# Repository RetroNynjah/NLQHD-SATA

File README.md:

# RetroNinja NLQHD-SATA
<br/>

A SATA-disk interface for the Commodore IEC-bus based on the NLQHD-lite design by Jochen Adler a.k.a. NLQ. The original design, documentation, firmware and source code can be found at [nlq.de](http://nlq.de).

## NLQ-HD
The NLQHD disk interface is a JiffyDOS compatible hard disk controller for the IEC bus. It was designed by Jochen Adler who also wrote the firmware. It supports a partition size of up to 128GB. Larger hard drives can be used but the partition size can not be greater than 128GB. 
The file system used is FAT32 so with a SATA-USB adapter it's easy to unplug and connect the SATA drive to a computer for quick file transfers.  
It should work with all Commodore 8-bit computers using an IEC bus. The drive can in theory be used with a stock kernal in the computer but the standard commands for navigating directories uses the command channel and are pretty cumbersome to use. A JiffyDOS kernal or one of it's derivatives such as S-JiffyDOS or JaffyDOS is pretty much required.

## NLQHD-SATA
This SATA version is a somewhat simplified design in that it doesn't have the same level of over-voltage protection as the original design has. The reason is that I wanted to keep the size of the design down (70x58mm) to fit in a 3D-printed enclosure. It also can't be powered by 1541-II PSU so the protection is less necessary than on the original design. I recommend that this version is powered using a decent quality 12V DC adapter with a center positive barrel connector.  
I have also removed the debugging/programming dip switches so the programming software for the C64 can't be used for flashing the firmware. I don't think it's safe to use so don't even try to use it!  
Instead I have added an ICSP programming header so that the firmware can be programmed in circuit using any AVR programmer such as AVR-ISP, USBASP or even an Arduino (Arduino as ISP). More importantly I've also added a JMH330 PATA-SATA bridge so that the interface can be used with more available and reliable SSD drives without an extra adapter. All SATA drives should be possible to use, from older 3.5" rotational drives to the newer 2.5" SSD drives. 
I replaced the sometimes hard-to-find 5 Volt regulator with integrated components based around an LM2596 voltage regulator. These have unfortunately also became harder to find from reliable sources at the time of writing but are easy to find on eBay or AliExpress. 3.3V and 1.8V voltage regulators have been added to drive the SATA bridge.  
I have made a separate front panel for the control buttons and LEDs. It connects to the mainboard using a 5 pin connector and can easily be replaced by a different panel if you need a different shape.  

<br/>
<br/>

I have also created a simple front panel board with buttons and status LEDs.  
This separate board should be pretty easy to modify to suite your own needs.
<br/>

## Mainboard BOM

|Parts|Device|Value|Qty|
|-----|-----|-----|-----|
|C101, C102, C103, C104, C201, C202, C203, C204, C205, C206, C301|Ceramic capacitor 0805|100n|11|
|C11, C12|Ceramic capacitor 0805|100p|2|
|C207, C208, C209, C210|Ceramic capacitor 0805|10n|4|
|C211|Ceramic capacitor 0805|1u 10V|1|
|C401|Electrolytic capacitor SMD 6.3X7.7|100u 25V|1|
|C403|Electrolytic capacitor SMD 6.3X7.7|220u 10V|1|
|C404|Ceramic capacitor 0805|10n(*)|1|
|C501, C502, C601, C602|Polarized tantalum capacitor 1206|10uF 10V|4|
|C9, C10, C212, C213|Ceramic capacitor 0805|22p|4|
|D1, D401|Schottky diode 3A SOD-123FL|S34|2|
|D12|General purpose diode SOD-323F|1N4148WSF|1|
|J1, J2|DIN-6 Female PCB-mount||2|
|J3|Molex 22-pin SATA host connector|0470184000|1|
|J4|DC Barrel Jack|PJ-002A|1|
|J5|Shrouded male JST header|5-pin, 2.0mm|1|
|J6|Pin header|2x3-pin, 2.54mm|1|
|JP1|Jumper or power switch|2-pin, 2.54mm|1|
|L1|Inductor 10x11mm|33uH|1|
|R11|Resistor 0805|10k|1|
|R201|Resistor 0805|12k|1|
|R202|Resistor 0805|47k|1|
|R203|Resistor 0805|1M|1|
|R401|Resistor 0805|1k (*)|1|
|R402|Resistor 0805|3k1/0R(*)|1|
|R5, R6|Resistor 0805|100R|2|
|SW1|Tact. switch right angle|6.0x5.0x8.5mm|1|
|U1|Microcontroller TQFP-44|ATmega1284(P)|1|
|U2|PATA-SATA bridge TQFP-64|JMH330|1|
|U3|Hex buffers/drivers SOIC14|74LS07|1|
|U4|Switching regulator TO263-5|LM2596 (AP1501A)|1|
|U5|Volt regulator 3.3V SOT-223|LD1117-3.3|1|
|U6|Volt regulator 1.8V SOT-223|LD1117-1.8|1|
|Y1|Crystal ECX-32|8MHz|1|
|Y2|Crystal ECX-32|25MHz|1|

(*) Only for Adjustable LM2596.
If using a fixed 5V LM2596: Do NOT install R401 and C404 and use a 0 Ohm resistor at R402

There are several variants of 6-pin DIN connectors with different foot prints. I have tried to accommodate them all in one single foot print. Let me know if you have a DIN connector that still doesn't fit this board.

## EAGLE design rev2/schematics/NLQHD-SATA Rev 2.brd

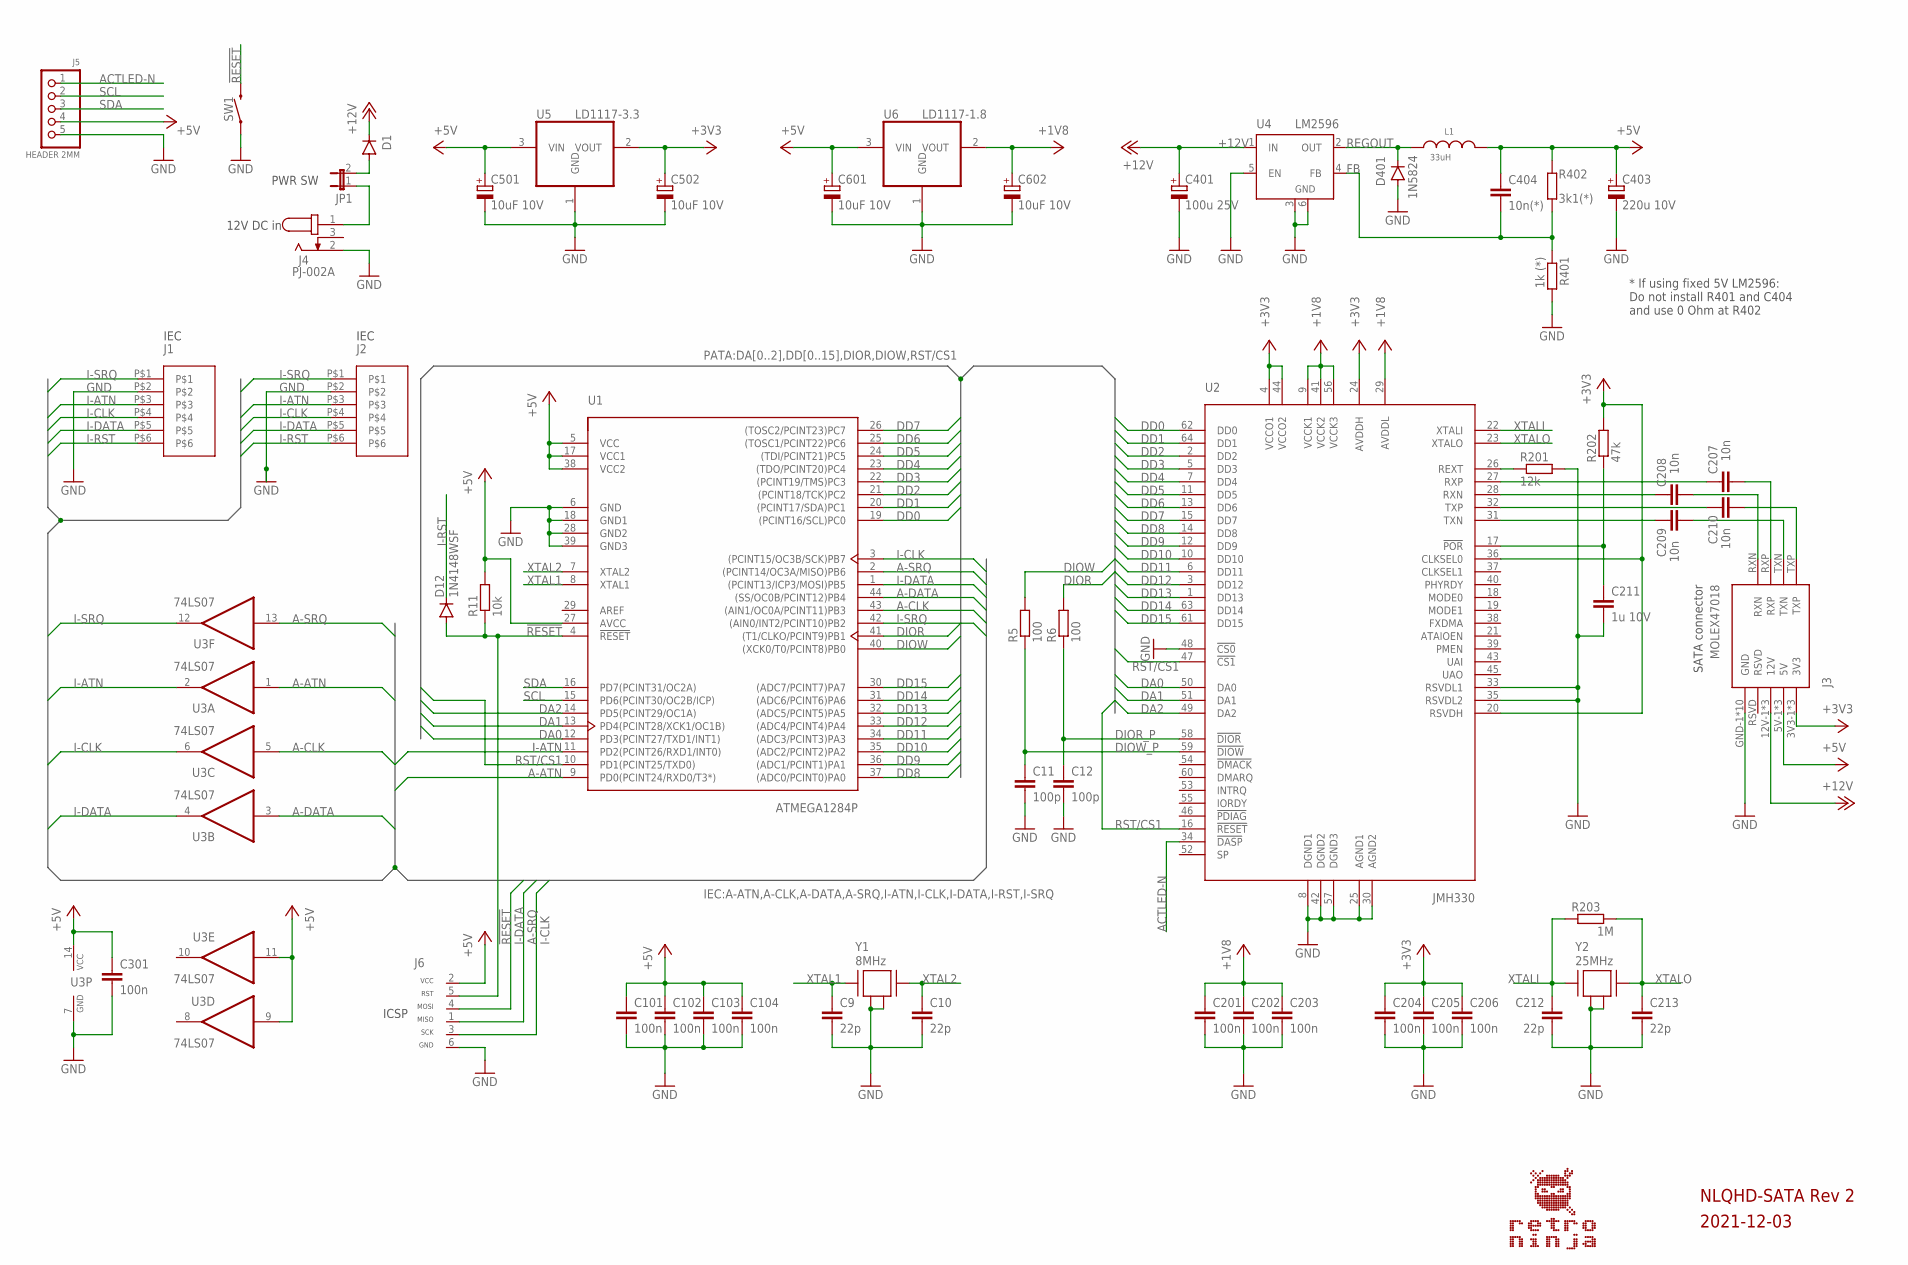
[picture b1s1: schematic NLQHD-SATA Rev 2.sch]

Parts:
C9, C10, C212, C213: 22p; C0805
C11, C12: 100p; C0805
C101, C102, C103, C104, C201, C202, C203, C204, C205, C206, C301: 100n; C0805
C207, C208, C209, C210: 10n; C0805
C211: 1u 10V; C0805
C401: 100u 25V; CAP_POL_SMD_6.3X7.7
C403: 220u 10V; CAP_POL_SMD_6.3X7.7
C404: 10n(*); C0805
C501, C502, C601, C602: 10uF 10V; A/3216-18R
D1: DIODE_SOD-123FL; SOD-123FL
D12: 1N4148WSF; SOD-323F
D401: 1N5824; SOD-123FL
J1, J2: DIN-6_PCB; DIN-6-PCB
J3: MOLEX47018; MOLEX47018SATA
J4: PJ-002A; CUI_PJ-002A
J5: HEADER 2MM; HEADER_1X5_2MM_JST
J6: ICSP_CONNECTOR_6_ALT; HEADER_2X3_ALT
JP1: JUMPER-2; HEADER_1X2
L1: 33uH; WE-LHMI_1040
R5, R6: 100; R0805
R11: 10k; R0805
R201: 12k; R0805
R202: 47k; R0805
R203: 1M; R0805
R401: 1k (*); R0805
R402: 3k1(*); R0805
SW1: SWITCH_MOMENTARY_6.0X5.0_RIGHT_ANGLE; SWITCH_MOM_6.0MMX5.0MM_RIGHT_ANGLE
U1: ATMEGA1284P; TQFP-44
U2: JMH330; TQFP-64_12X12X1.20
U3: 74LS07; SOIC14
U4: LM2596; TO263-5
U5: LD1117-3.3; SOT223
U6: LD1117-1.8; SOT223
Y1: 8MHz; ECX-32
Y2: 25MHz; ECX-32

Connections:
!POR: C211.1, R202.1, U2.17 (!POR)
!RESET: D12.A, J6.5 (RST), R11.1, SW1.2, U1.4 (!RESET)
+1V8: C201.1, C202.1, C203.1, C602.+, U2.9 (VCCK1), U2.29 (AVDDL), U2.41 (VCCK2), U2.56 (VCCK3), U6.2 (VOUT)
+3V3: C204.1, C205.1, C206.1, C502.+, J3.3V3-1 (3V3), J3.3V3-2 (3V3), J3.3V3-3 (3V3), R202.2, U2.4 (VCCO1), U2.20 (RSVDH), U2.24 (AVDDH), U2.36 (CLKSEL0), U2.44 (VCCO2), U5.2 (VOUT)
+5V: C101.1, C102.1, C103.1, C104.1, C301.1, C403.+, C404.1, C501.+, C601.+, J3.5V-1 (5V), J3.5V-2 (5V), J3.5V-3 (5V), J5.4, J6.2 (VCC), L1.2, R11.2, R402.2, U1.5 (VCC), U1.17 (VCC1), U1.27 (AVCC), U1.38 (VCC2), U3.9 (I), U3.11 (I), U3.14 (VCC), U5.3 (VIN), U6.3 (VIN)
+12V: C401.+, D1.C, J3.12V-1 (12V), J3.12V-2 (12V), J3.12V-3 (12V), U4.1 (IN)
+12V-IN: J4.1, JP1.1
A-ATN: U1.9 (PD0(PCINT24/RXD0/T3*)), U3.1 (I)
A-CLK: U1.43 ((AIN1/OC0A/PCINT11)PB3), U3.5 (I)
A-DATA: U1.44 ((SS/OC0B/PCINT12)PB4), U3.3 (I)
A-SRQ: J6.1 (MISO), U1.2 ((PCINT14/OC3A/MISO)PB6), U3.13 (I)
ACTLED-N: J5.1, U2.34 (!DASP)
DA0: U1.12 (PD3(PCINT27/TXD1/INT1)), U2.50 (DA0)
DA1: U1.13 (PD4(PCINT28/XCK1/OC1B)), U2.51 (DA1)
DA2: U1.14 (PD5(PCINT29/OC1A)), U2.49 (DA2)
DD0: U1.19 ((PCINT16/SCL)PC0), U2.62 (DD0)
DD1: U1.20 ((PCINT17/SDA)PC1), U2.64 (DD1)
DD2: U1.21 ((PCINT18/TCK)PC2), U2.2 (DD2)
DD3: U1.22 ((PCINT19/TMS)PC3), U2.5 (DD3)
DD4: U1.23 ((TDO/PCINT20)PC4), U2.7 (DD4)
DD5: U1.24 ((TDI/PCINT21)PC5), U2.11 (DD5)
DD6: U1.25 ((TOSC1/PCINT22)PC6), U2.13 (DD6)
DD7: U1.26 ((TOSC2/PCINT23)PC7), U2.15 (DD7)
DD8: U1.37 ((ADC0/PCINT0)PA0), U2.14 (DD8)
DD9: U1.36 ((ADC1/PCINT1)PA1), U2.12 (DD9)
DD10: U1.35 ((ADC2/PCINT2)PA2), U2.10 (DD10)
DD11: U1.34 ((ADC3/PCINT3)PA3), U2.6 (DD11)
DD12: U1.33 ((ADC4/PCINT4)PA4), U2.3 (DD12)
DD13: U1.32 ((ADC5/PCINT5)PA5), U2.1 (DD13)
DD14: U1.31 ((ADC6/PCINT6)PA6), U2.63 (DD14)
DD15: U1.30 ((ADC7/PCINT7)PA7), U2.61 (DD15)
DIOR: R6.2, U1.41 ((T1/CLKO/PCINT9)PB1)
DIOR_P: C12.1, R6.1, U2.58 (!DIOR)
DIOW: R5.2, U1.40 ((XCK0/T0/PCINT8)PB0)
DIOW_P: C11.1, R5.1, U2.59 (!DIOW)
FB: C404.2, R401.1, R402.1, U4.4 (FB)
GND: C9.2, C10.2, C11.2, C12.2, C101.2, C102.2, C103.2, C104.2, C201.2, C202.2, C203.2, C204.2, C205.2, C206.2, C211.2, C212.2, C213.2, C301.2, C401.-, C403.-, C501.-, C502.-, C601.-, C602.-, D401.A, J1.P$2, J2.P$2, J3.GND-1 (GND), J3.GND-2 (GND), J3.GND-3 (GND), J3.GND-4 (GND), J3.GND-5 (GND), J3.GND-6 (GND), J3.GND-7 (GND), J3.GND-8 (GND), J3.GND-9 (GND), J3.GND-10 (GND), J4.2, J5.5, J6.6 (GND), R201.2, R401.2, SW1.1, U1.6 (GND), U1.18 (GND1), U1.28 (GND2), U1.39 (GND3), U2.8 (DGND1), U2.25 (AGND1), U2.30 (AGND2), U2.33 (RSVDL1), U2.35 (RSVDL2), U2.42 (DGND2), U2.48 (!CS0), U2.57 (DGND3), U3.7 (GND), U4.3 (GND), U4.5 (EN), U4.6 (GND), U5.1 (GND), U6.1 (GND), Y1.2, Y1.4, Y2.2, Y2.4
I-ATN: J1.P$3, J2.P$3, U1.11 (PD2(PCINT26/RXD1/INT0)), U3.2 (O)
I-CLK: J1.P$4, J2.P$4, J6.3 (SCK), U1.3 ((PCINT15/OC3B/SCK)PB7), U3.6 (O)
I-DATA: J1.P$5, J2.P$5, J6.4 (MOSI), U1.1 ((PCINT13/ICP3/MOSI)PB5), U3.4 (O)
I-RST: D12.C, J1.P$6, J2.P$6
I-SRQ: J1.P$1, J2.P$1, U1.42 ((AIN0/INT2/PCINT10)PB2), U3.12 (O)
unnamed: R201.1, U2.26 (REXT)
unnamed: D1.A, JP1.2
unnamed: C207.2, J3.RXP
unnamed: C208.2, J3.RXN
unnamed: C210.2, J3.TXP
unnamed: C209.2, J3.TXN
unnamed: C208.1, U2.28 (RXN)
unnamed: C209.1, U2.31 (TXN)
unnamed: C210.1, U2.32 (TXP)
unnamed: C207.1, U2.27 (RXP)
REGOUT: D401.C, L1.1, U4.2 (OUT)
RST/CS1: U1.10 (PD1(PCINT25/TXD0)), U2.16 (!RESET), U2.47 (!CS1)
SCL: J5.2, U1.15 (PD6(PCINT30/OC2B/ICP))
SDA: J5.3, U1.16 (PD7(PCINT31/OC2A))
XTAL1: C9.1, U1.8 (XTAL1), Y1.1
XTAL2: C10.1, U1.7 (XTAL2), Y1.3
XTALI: C212.1, R203.1, U2.22 (XTALI), Y2.1
XTALO: C213.1, R203.2, U2.23 (XTALO), Y2.3

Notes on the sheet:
SATA connector
12V DC in
IEC
PWR SW
ICSP
2021-12-03
* If using fixed 5V LM2596: Do not install R401 and C404 and use 0 Ohm at R402
NLQHD-SATA Rev 2

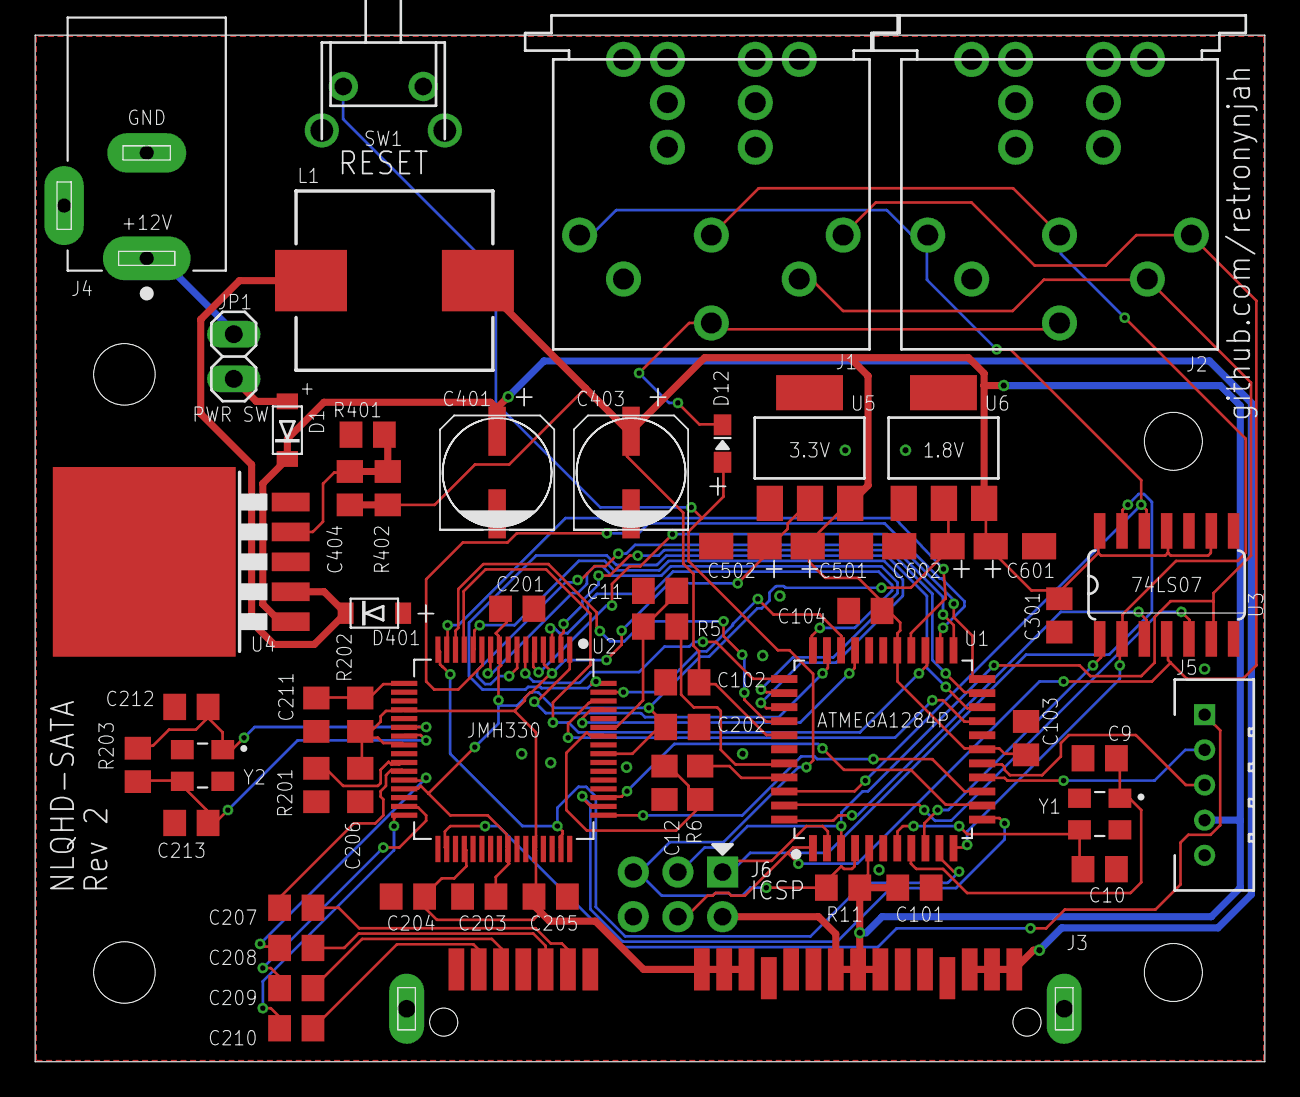
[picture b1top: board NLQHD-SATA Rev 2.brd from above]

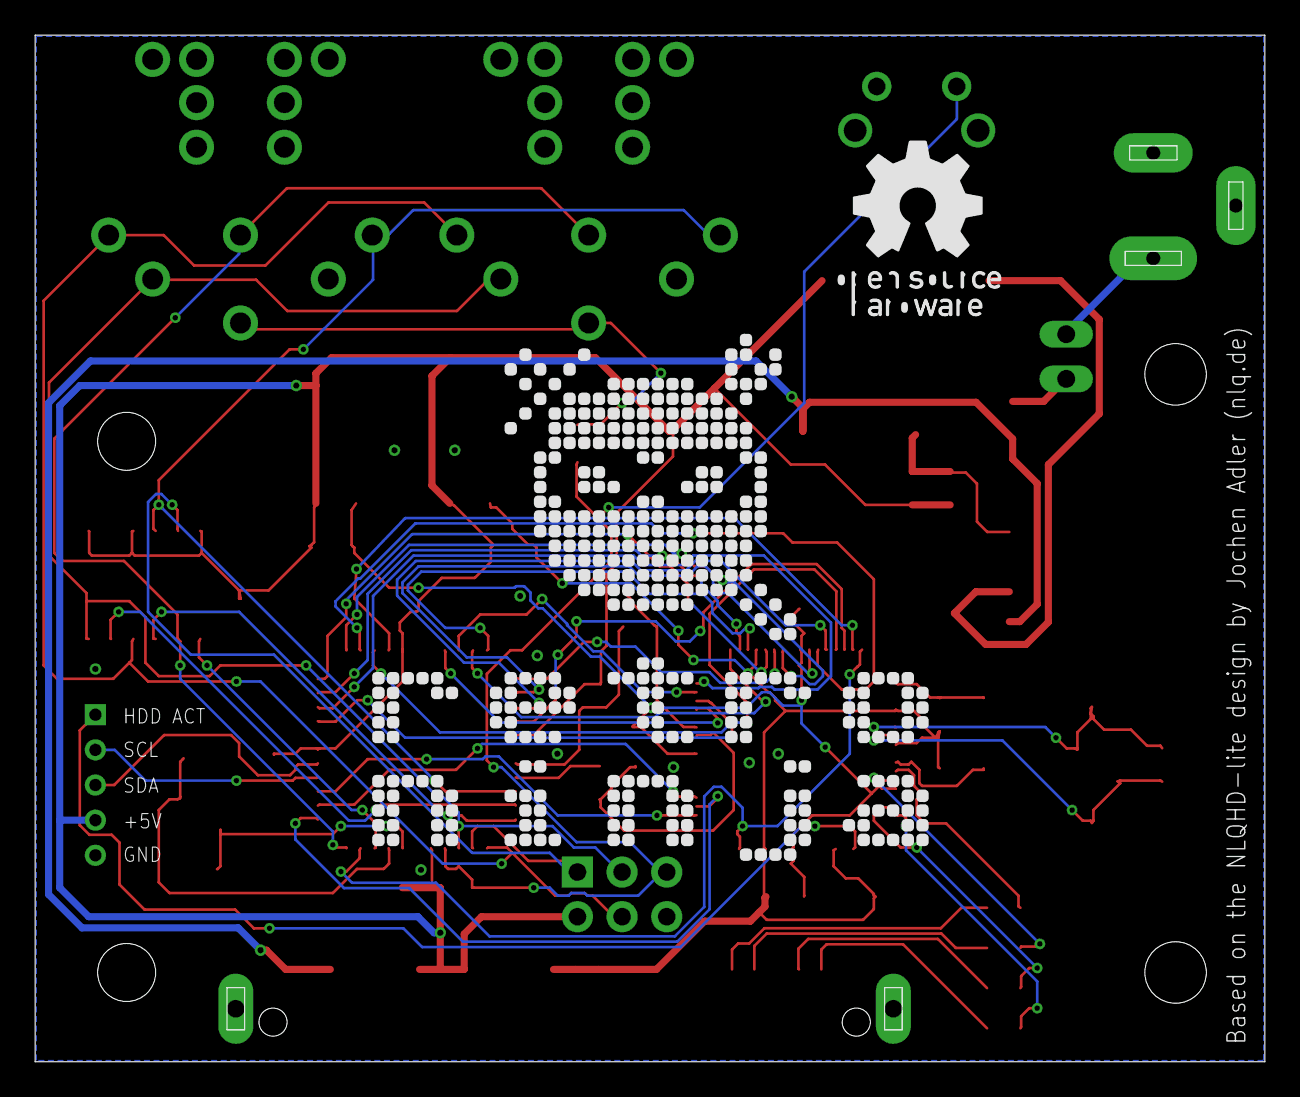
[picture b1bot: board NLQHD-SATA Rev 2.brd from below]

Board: 2 copper layers, 70.0 x 58.4 mm, 59 parts (2 on the bottom side), 60 nets.

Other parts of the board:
U$1: RETRONINJA_30MM
U$2: OSHW_10MM

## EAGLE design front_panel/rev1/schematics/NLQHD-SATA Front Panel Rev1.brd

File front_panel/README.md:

A front panel for the NLQHD-SATA

<br/>

## BOM
|Parts|Device|Value|Qty|
|-----|-----|-----|-----|
|SW2, SW3|Tact switch|6.0x6.0x9.0mm|2|
|D7|3mm LED|Yellow|1|
|D8|3mm LED|Green|1|
|D9|3mm LED|Red|1|
|D2, D3|General purpose diode SOD-323F|1N4148WSF|2|
|R7, R8, R9|Resistor 0805|560R|3|

Choose resistors that work with the actual LEDs you have on hand. Many super bright LEDs need a lot more resistance to not be blindingly bright.

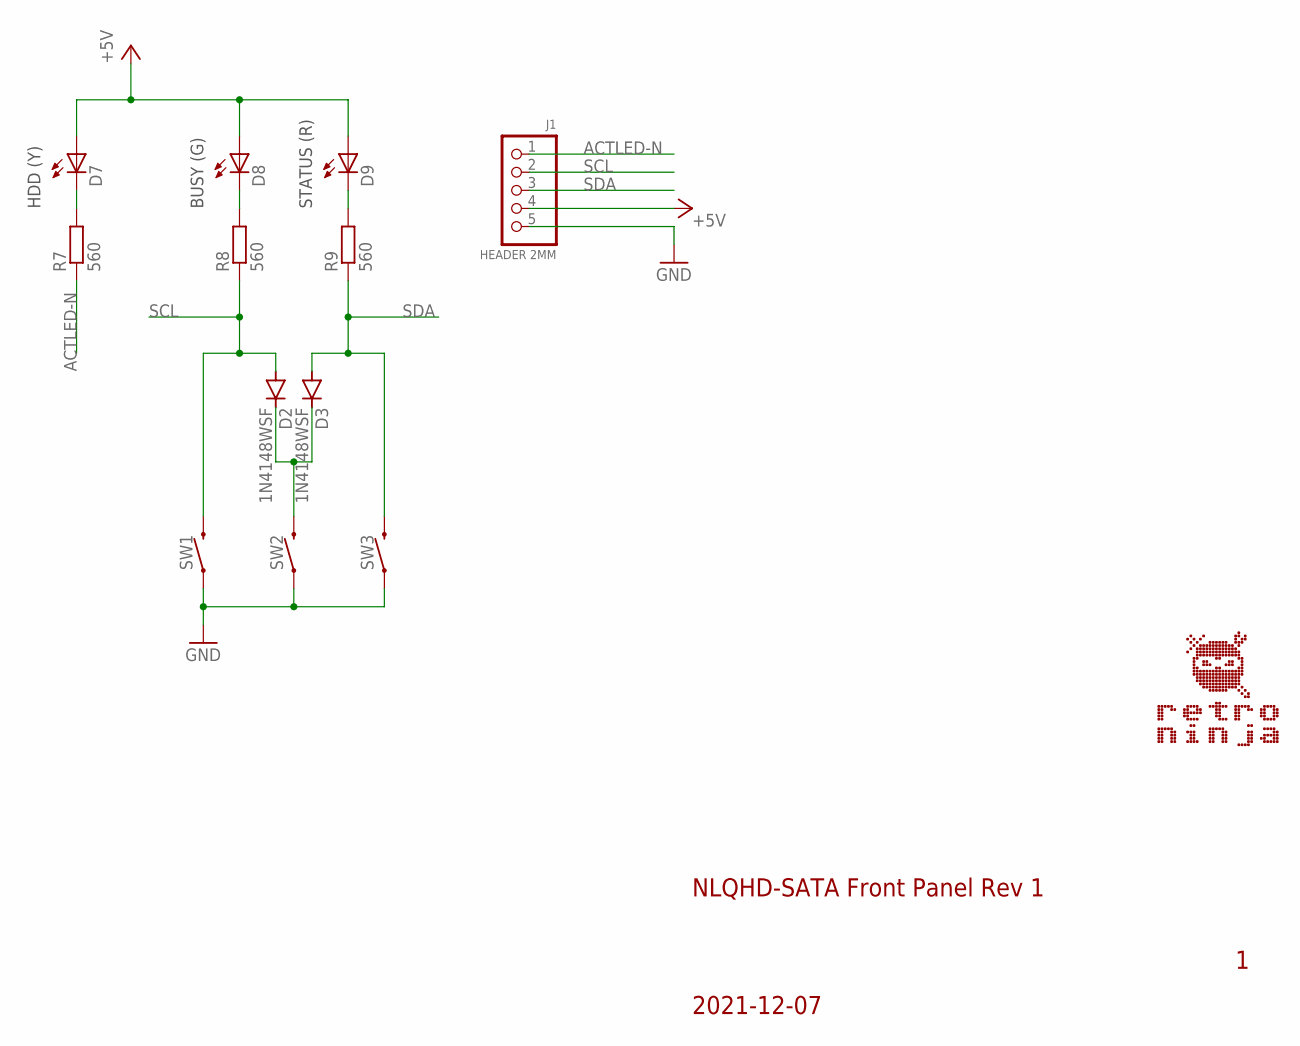
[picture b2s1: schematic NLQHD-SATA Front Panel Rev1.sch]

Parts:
D2, D3: 1N4148WSF; SOD-323F
D7: LED_3MM_RED; LED3MM_RED
D8, D9: LED_3MM_GREEN; LED3MM_GREEN
J1: HEADER 2MM; HEADER_1X5_2MM_JST
R7, R8, R9: 560; R0805
SW1, SW2, SW3: SWITCH_MOMENTARY_6.0X5.0; SWITCH_MOM_6.0MMX5.0MM

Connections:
+5V: D7.A, D8.A, D9.A, J1.4
ACTLED-N: J1.1, R7.1
ACTLED-RES: D7.K (C), R7.2
BUSYLED-RES: D8.K (C), R8.2
GND: J1.5, SW1.1, SW1.2 (1), SW2.1, SW2.2 (1), SW3.1, SW3.2 (1)
unnamed: D2.C, D3.C, SW2.3 (2), SW2.4 (2)
SCL: D2.A, J1.2, R8.1, SW1.3 (2), SW1.4 (2)
SDA: D3.A, J1.3, R9.1, SW3.3 (2), SW3.4 (2)
STATLED-RES: D9.K (C), R9.2

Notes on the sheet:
BUSY (G)
HDD (Y)
STATUS (R)
NLQHD-SATA Front Panel Rev 1
2021-12-07

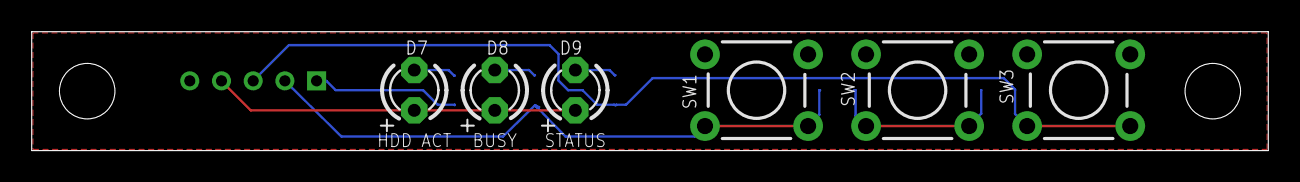
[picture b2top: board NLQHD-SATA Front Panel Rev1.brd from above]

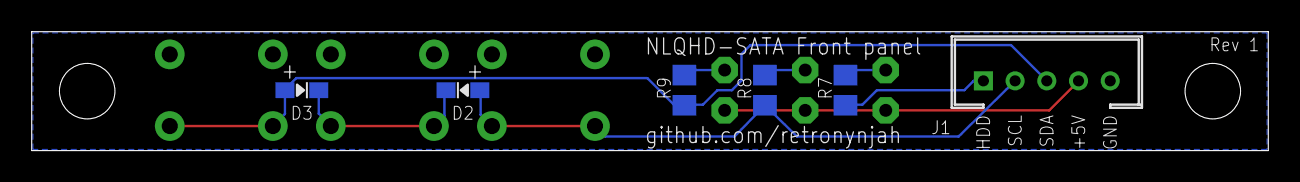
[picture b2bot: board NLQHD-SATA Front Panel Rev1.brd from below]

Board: 2 copper layers, 78.0 x 7.5 mm, 12 parts (6 on the bottom side), 9 nets.

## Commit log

2022-03-14 Upload
2022-06-22 Update NLQHD-SATA User's Guide.pdf
    Added section about copying error messages to EEPROM
    Corrected some minor errors.

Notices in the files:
parts and their libraries:
Wurth_Power Magnetics_WE-LHMI: Copyright: Würth Elektronik
